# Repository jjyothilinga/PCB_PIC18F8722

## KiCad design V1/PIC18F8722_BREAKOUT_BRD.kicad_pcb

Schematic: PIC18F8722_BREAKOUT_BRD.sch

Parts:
C1: 10uF/16V
C2, C3, C4, C5, C6, C7: 0.1uF
C8: 1uF/16V
D1: LED
D2: PWR_LED
IC1: PIC18F8722; microchip-2-TQFP80
P1: PGM_CONN
P2: CONN _1_20
P3: CONN_21_40
P4: CONN_41_60
P5: CONN_61_80
P7, P9: PWR_CON
R1, R4: 10K
R2: 1K2
R3: 1K
SW1: SW_PUSH

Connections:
/AVDD: C1.1, C2.1, C3.1, C4.1, C5.1, C6.1, C7.1, IC1.12 (VDD), IC1.25 (AVDD), IC1.32 (VDD@1), IC1.48 (VDD@2), IC1.71 (VDD@3), P1.2, P2.12, P3.5, P3.12, P4.8, P5.11, P7.2 (PM), P9.2 (PM), R1.1, R2.1, R3.1, R4.1
/HB_LED: D1.2 (K), IC1.5 (RG0/ECCP3/P3A), P2.5
/MCLR: C8.1, IC1.9 (RG5/-MCLR/VPP), P1.1, P2.9, R4.2, SW1.2
/PGC: IC1.52 (RB6/KBI2/PGC), P1.5, P4.12
/PGD: IC1.47 (RB7/KBI3/PGD), P1.4, P4.7
/RA0: IC1.30 (RA0/AN0), P3.10
/RA1: IC1.29 (RA1/AN1), P3.9
/RA2: IC1.28 (RA2/AN2/VREF-), P3.8
/RA3: IC1.27 (RA3/AN3/VREF+), P3.7
/RA4: IC1.34 (RA4/T0CKI), P3.14, R1.2
/RA5: IC1.33 (RA5/AN4/HLVDIN), P3.13
/RA6: IC1.50 (OSC2/CLKO/RA6), P4.10
/RA7: IC1.49 (OSC1/CLKI/RA7), P4.9
/RB0: IC1.58 (RB0/INT0), P4.18
/RB1: IC1.57 (RB1/INT1), P4.17
/RB2: IC1.56 (RB2/INT2), P4.16
/RB3: IC1.55 (RB3/INT3/ECCP2/P2A), P4.15
/RB4: IC1.54 (RB4/KBI0), P4.14
/RB5: IC1.53 (RB5/KBI1/PGM), P4.13
/RC0: IC1.36 (RC0/T1OSO/T13CKI), P3.16
/RC1: IC1.35 (RC1/T1OSI/ECCP2/P2A), P3.15
/RC2: IC1.43 (RC2/ECCP1/P1A), P4.3
/RC3: IC1.44 (RC3/SCK1/SCL1), P4.4
/RC4: IC1.45 (RC4/SDI1/SDA1), P4.5
/RC5: IC1.46 (RC5/SDO1), P4.6
/RC6: IC1.37 (RC6/TX1/CK1), P3.17
/RC7: IC1.38 (RC7/RX1/DT1), P3.18
/RD0: IC1.72 (RD0/AD0/PSP0), P5.12
/RD1: IC1.69 (RD1/AD1/PSP1), P5.9
/RD2: IC1.68 (RD2/AD2/PSP2), P5.8
/RD3: IC1.67 (RD3/AD3/PSP3), P5.7
/RD4: IC1.66 (RD4/AD4/PSP4/SDO2), P5.6
/RD5: IC1.65 (RD5/AD5/PSP5/SDI2/SDA2), P5.5
/RD6: IC1.64 (RD6/AD6/PSP6/SCK2/SCL2), P5.4
/RD7: IC1.63 (RD7/AD7/PSP7/-SS2), P5.3
/RE0: IC1.4 (RE0/AD8/-RD/P2D), P2.4
/RE1: IC1.3 (RE1/AD9/-WR/P2C), P2.3
/RE2: IC1.78 (RE2/AD10/-CS/P2B), P5.18
/RE3: IC1.77 (RE3/AD11/P3C), P5.17
/RE4: IC1.76 (RE4/AD12/P3B), P5.16
/RE5: IC1.75 (RE5/AD13/P1C), P5.15
/RE6: IC1.74 (RE6/AD14/P1B), P5.14
/RE7: IC1.73 (RE7/AD15/ECCP2/P2A), P5.13
/RF0: IC1.24 (RF0/AN5), P3.4
/RF1: IC1.23 (RF1/AN6/C2OUT), P3.3
/RF2: IC1.18 (RF2/AN7/C1OUT), P2.18
/RF3: IC1.17 (RF3/AN8), P2.17
/RF4: IC1.16 (RF4/AN9), P2.16
/RF5: IC1.15 (RF5/AN10/CVREF), P2.15
/RF6: IC1.14 (RF6/AN11), P2.14
/RF7: IC1.13 (RF7/-SS1), P2.13
/RG1: IC1.6 (RG1/TX2/CK2), P2.6
/RG2: IC1.7 (RG2/RX2/DT2), P2.7
/RG3: IC1.8 (RG3/CCP4/P3D), P2.8
/RG4: IC1.10 (RG4/CCP4/C3D), P2.10
/RH0: IC1.79 (RH0/A16), P5.19
/RH1: IC1.80 (RH1/A17), P5.20
/RH2: IC1.1 (RH2/A18), P2.1
/RH3: IC1.2 (RH3/A19), P2.2
/RH4: IC1.22 (RH4/AN12/P3C), P3.2
/RH5: IC1.21 (RH5/AN13/P3B), P3.1
/RH6: IC1.20 (RH6/AN14/P1C), P2.20
/RH7: IC1.19 (RH7/AN15/P1B), P2.19
/RJ0: IC1.62 (RJ0/ALE), P5.2
/RJ1: IC1.61 (RJ1/-OE), P5.1
/RJ2: IC1.60 (RJ2/-WRL), P4.20
/RJ3: IC1.59 (RJ3/-WRH), P4.19
/RJ4: IC1.39 (RJ4/BA0), P3.19
/RJ5: IC1.40 (RJ5/-CE), P3.20
/RJ6: IC1.41 (RJ6/-LB), P4.1
/RJ7: IC1.42 (RJ7/-UB), P4.2
GND: C1.2, C2.2, C3.2, C4.2, C5.2, C6.2, C7.2, C8.2, D2.2 (K), IC1.11 (VSS), IC1.26 (AVSS), IC1.31 (VSS@1), IC1.51 (VSS@2), IC1.70 (VSS@3), P1.3, P2.11, P3.6, P3.11, P4.11, P5.10, P7.1, P9.1, SW1.1
unnamed: D2.1 (A), R3.2
unnamed: D1.1 (A), R2.2

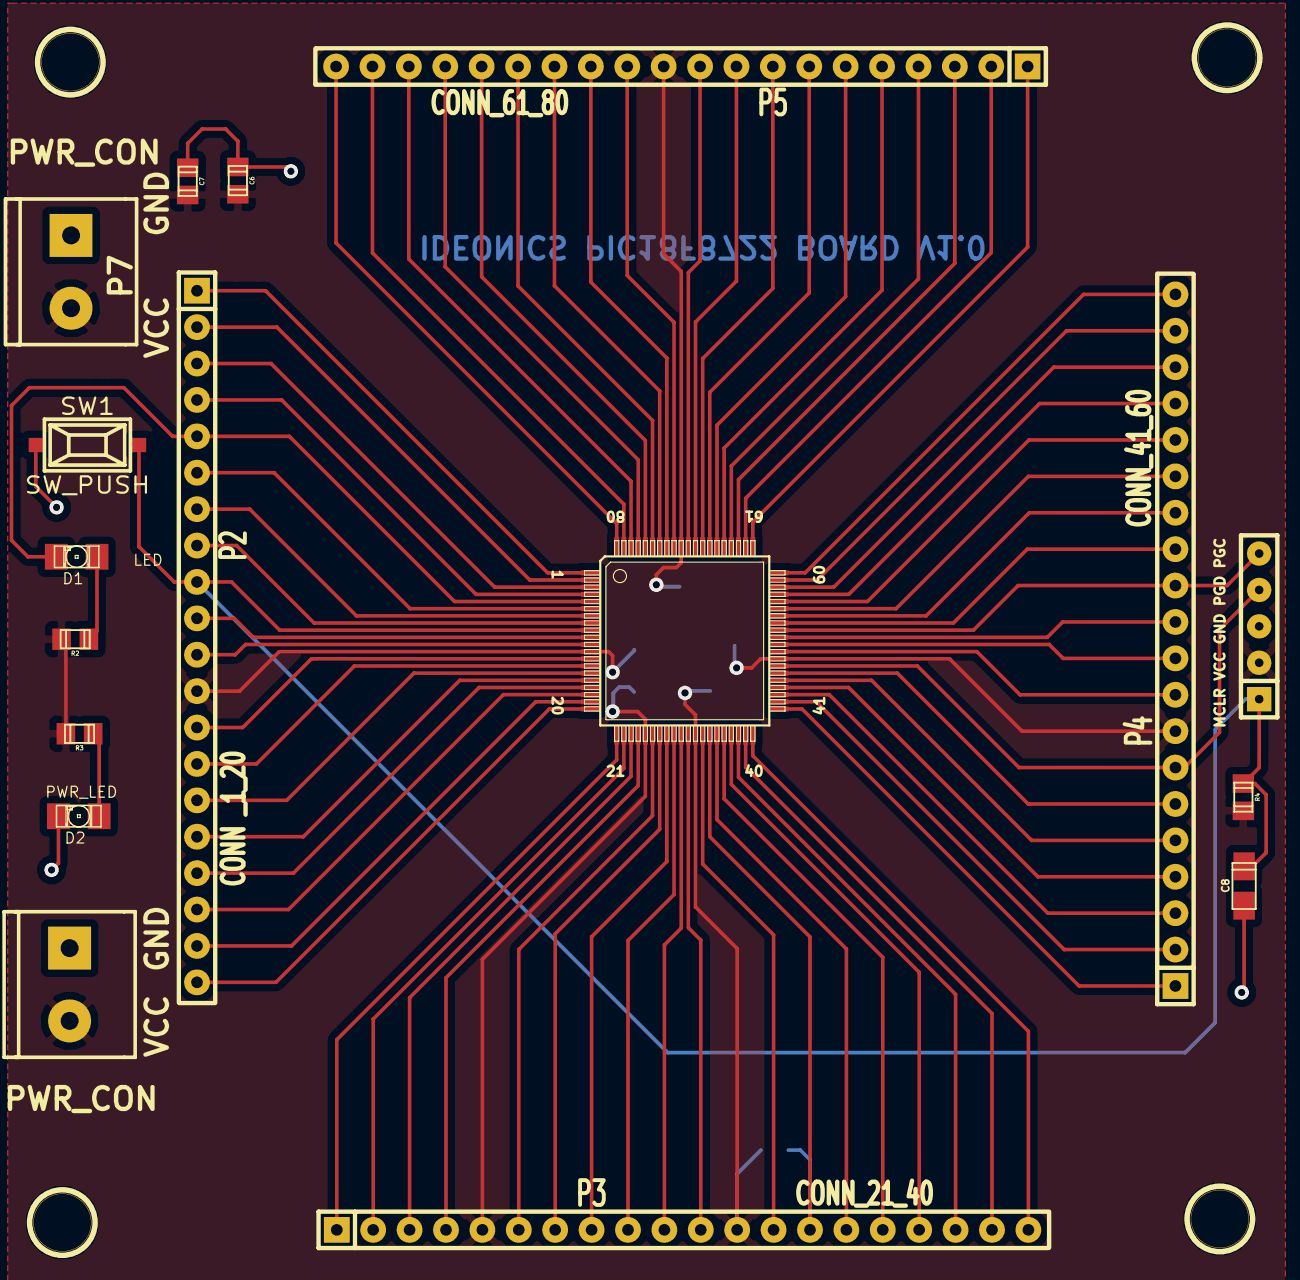
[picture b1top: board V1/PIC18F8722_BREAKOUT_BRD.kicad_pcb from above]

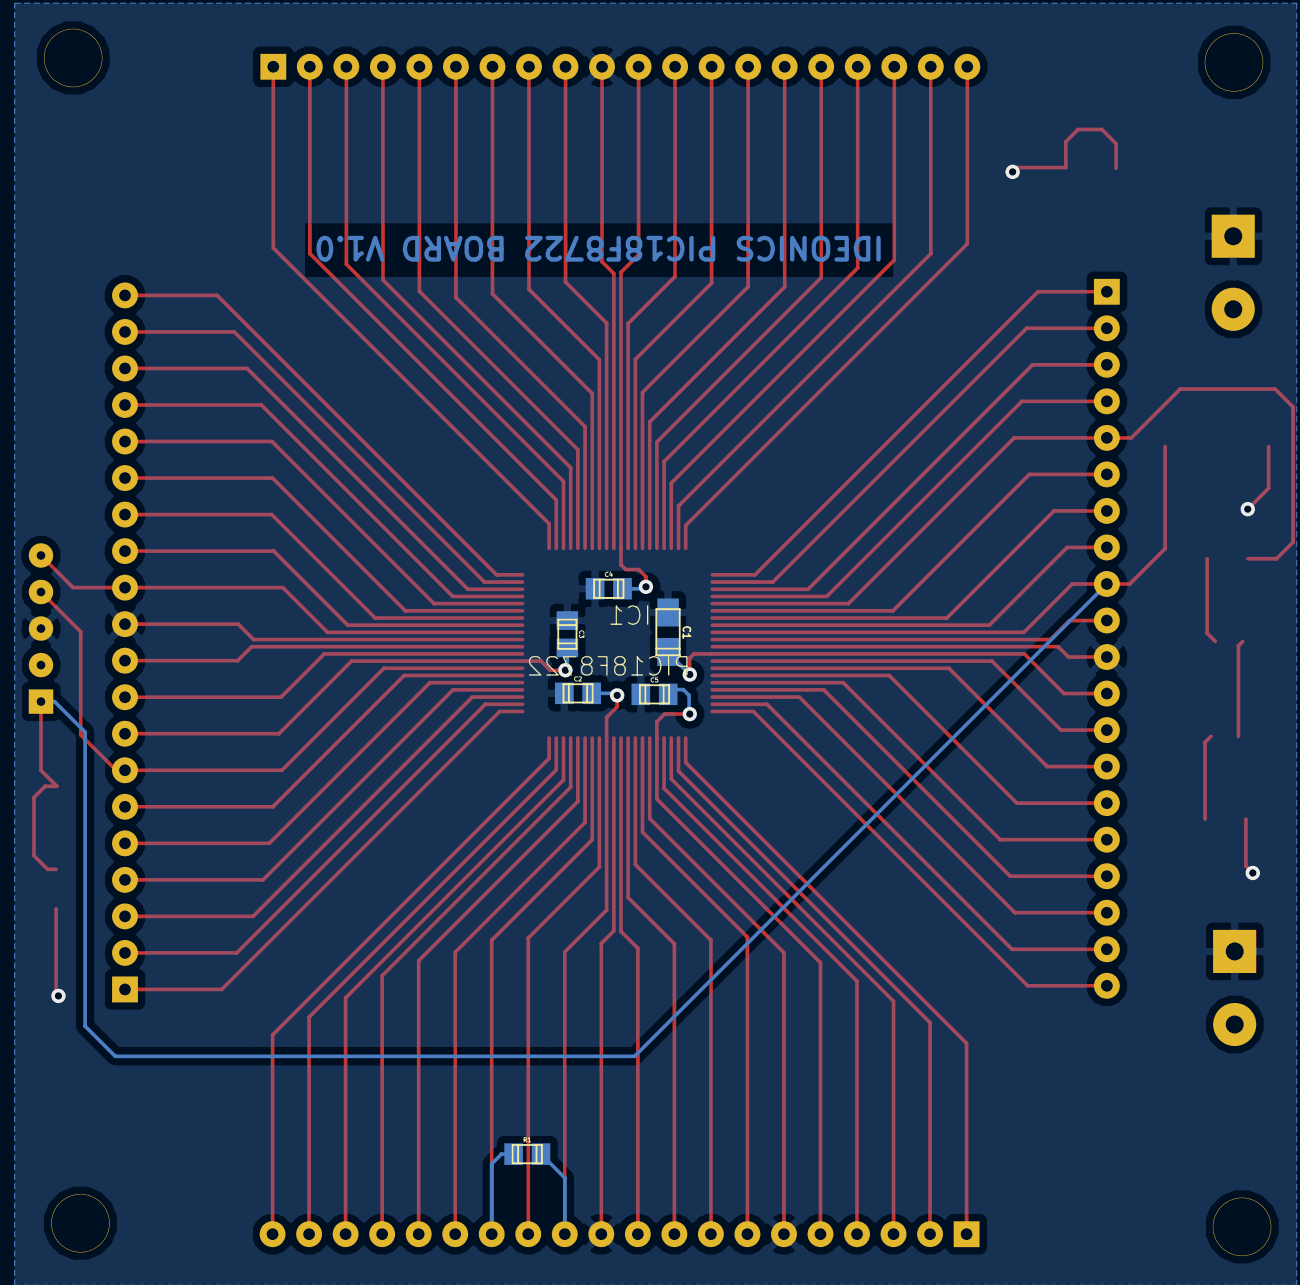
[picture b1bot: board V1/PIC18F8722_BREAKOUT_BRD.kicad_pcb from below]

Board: 2 copper layers, 27 parts (6 on the bottom side), 74 nets.

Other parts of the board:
1PIN, 1PIN#2, 1PIN#3, 1PIN#4: P***; 1pin

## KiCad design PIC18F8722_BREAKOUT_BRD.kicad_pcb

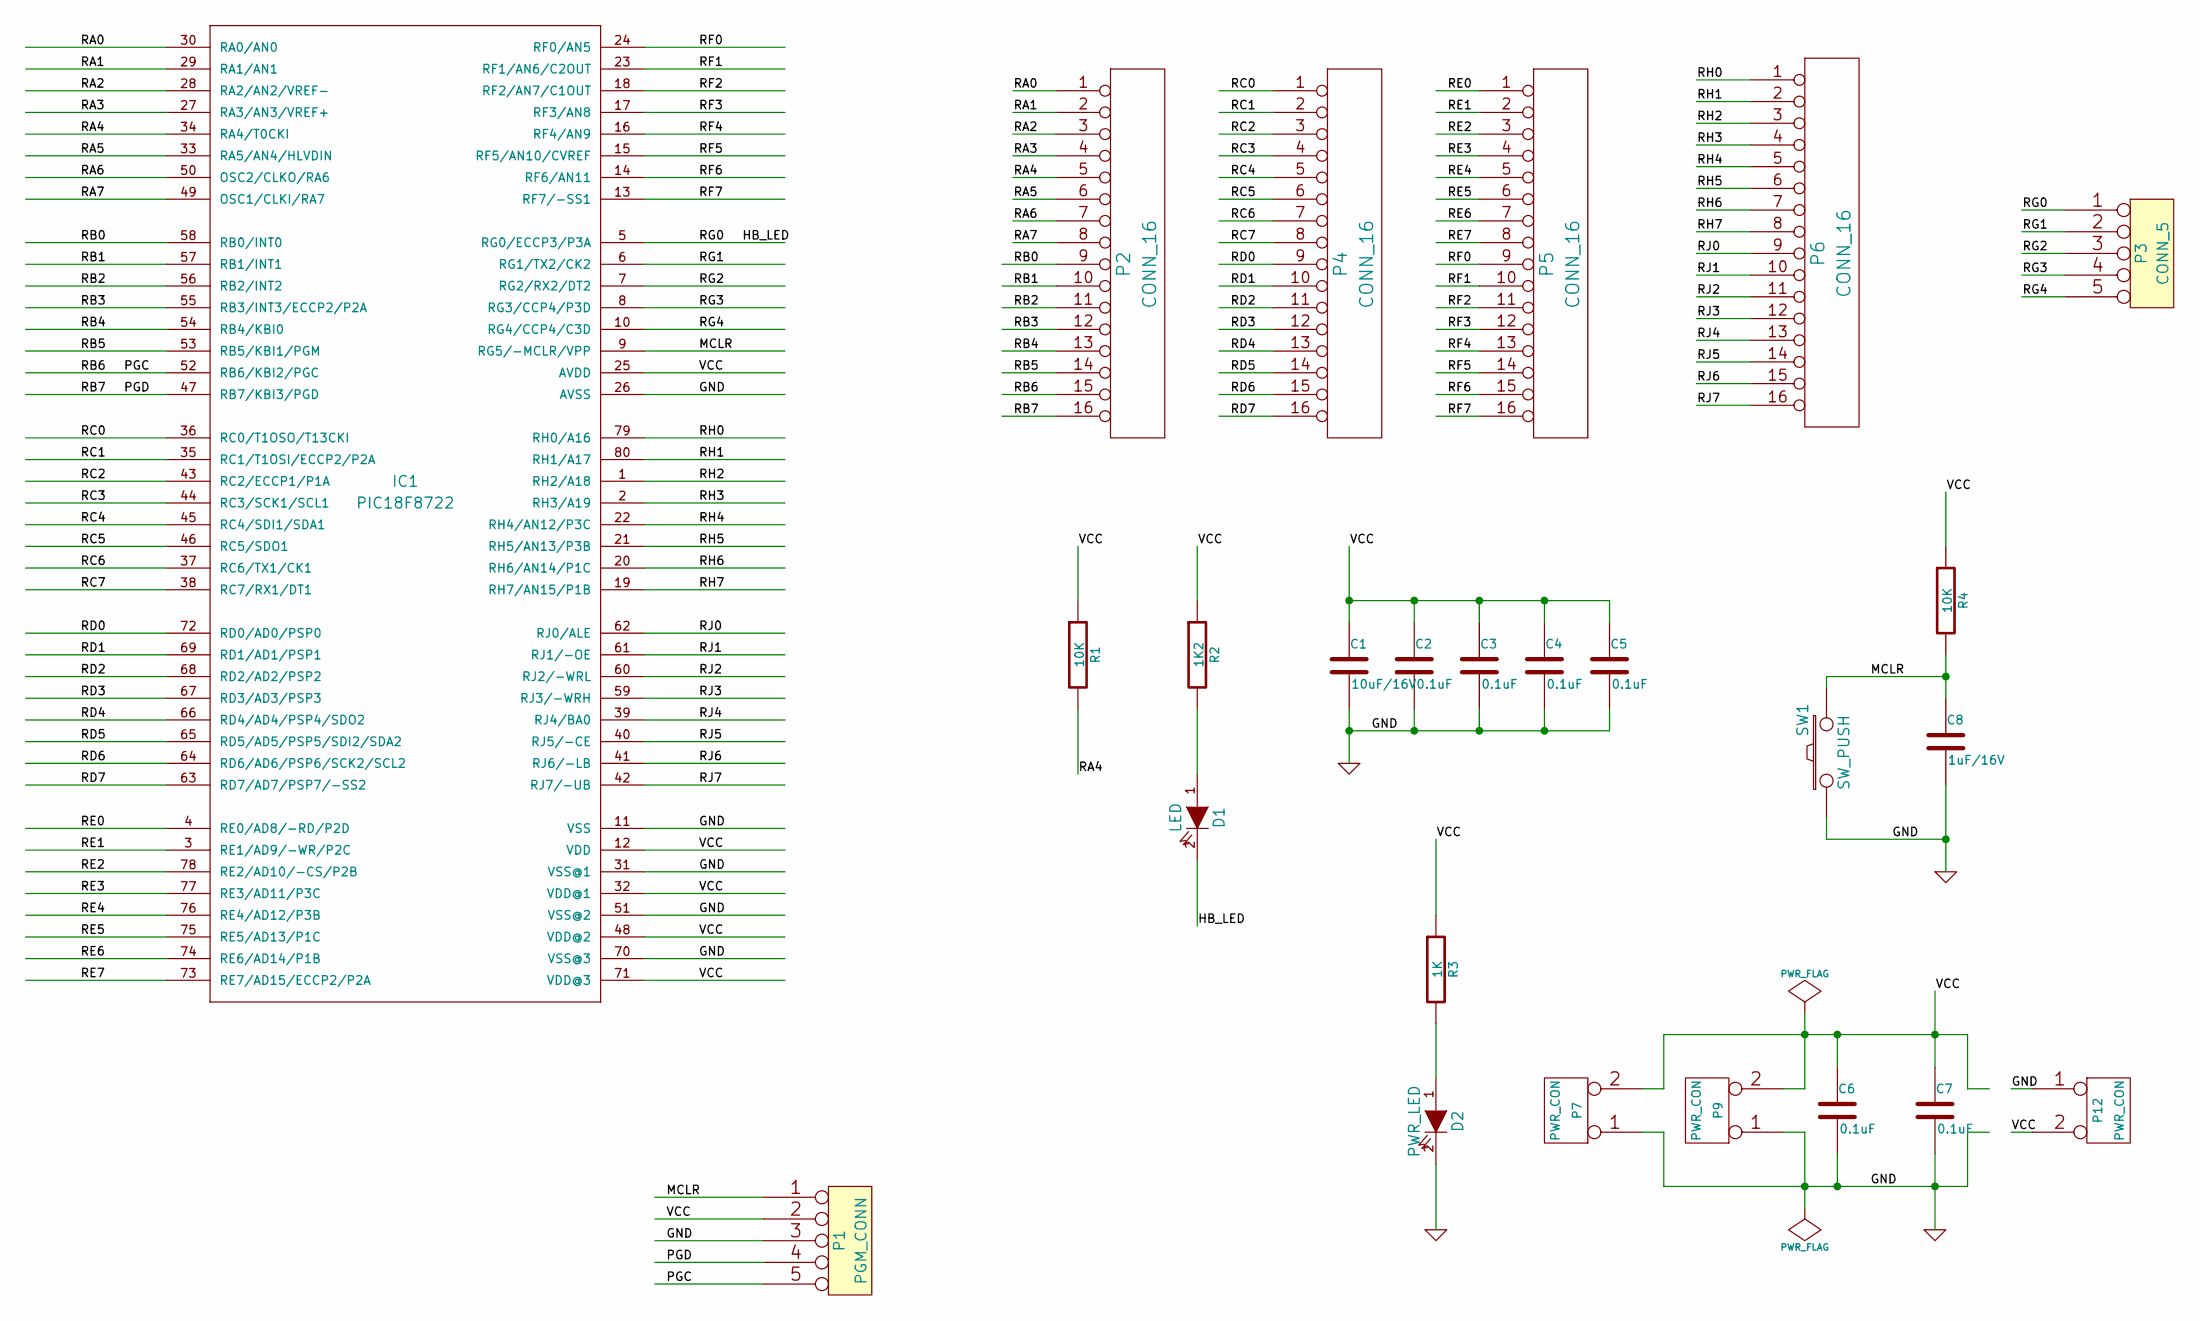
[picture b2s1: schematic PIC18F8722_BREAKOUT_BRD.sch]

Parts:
C1: 10uF/16V
C2, C3, C4, C5, C6, C7: 0.1uF
C8: 1uF/16V
D1: LED
D2: PWR_LED
IC1: PIC18F8722; microchip-2-TQFP80
P1: PGM_CONN
P2, P4, P5, P6: CONN_16
P3: CONN_5
P7, P9, P12: PWR_CON
R1, R4: 10K
R2: 1K2
R3: 1K
SW1: SW_PUSH

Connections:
/HB_LED: D1.2 (K), IC1.5 (RG0/ECCP3/P3A), P3.1
/MCLR: C8.1, IC1.9 (RG5/-MCLR/VPP), P1.1, R4.2, SW1.2
/PGC: IC1.52 (RB6/KBI2/PGC), P1.5, P2.15
/PGD: IC1.47 (RB7/KBI3/PGD), P1.4, P2.16
/RA0: IC1.30 (RA0/AN0), P2.1
/RA1: IC1.29 (RA1/AN1), P2.2
/RA2: IC1.28 (RA2/AN2/VREF-), P2.3
/RA3: IC1.27 (RA3/AN3/VREF+), P2.4
/RA4: IC1.34 (RA4/T0CKI), P2.5, R1.2
/RA5: IC1.33 (RA5/AN4/HLVDIN), P2.6
/RA6: IC1.50 (OSC2/CLKO/RA6), P2.7
/RA7: IC1.49 (OSC1/CLKI/RA7), P2.8
/RB0: IC1.58 (RB0/INT0), P2.9
/RB1: IC1.57 (RB1/INT1), P2.10
/RB2: IC1.56 (RB2/INT2), P2.11
/RB3: IC1.55 (RB3/INT3/ECCP2/P2A), P2.12
/RB4: IC1.54 (RB4/KBI0), P2.13
/RB5: IC1.53 (RB5/KBI1/PGM), P2.14
/RC0: IC1.36 (RC0/T1OSO/T13CKI), P4.1
/RC1: IC1.35 (RC1/T1OSI/ECCP2/P2A), P4.2
/RC2: IC1.43 (RC2/ECCP1/P1A), P4.3
/RC3: IC1.44 (RC3/SCK1/SCL1), P4.4
/RC4: IC1.45 (RC4/SDI1/SDA1), P4.5
/RC5: IC1.46 (RC5/SDO1), P4.6
/RC6: IC1.37 (RC6/TX1/CK1), P4.7
/RC7: IC1.38 (RC7/RX1/DT1), P4.8
/RD0: IC1.72 (RD0/AD0/PSP0), P4.9
/RD1: IC1.69 (RD1/AD1/PSP1), P4.10
/RD2: IC1.68 (RD2/AD2/PSP2), P4.11
/RD3: IC1.67 (RD3/AD3/PSP3), P4.12
/RD4: IC1.66 (RD4/AD4/PSP4/SDO2), P4.13
/RD5: IC1.65 (RD5/AD5/PSP5/SDI2/SDA2), P4.14
/RD6: IC1.64 (RD6/AD6/PSP6/SCK2/SCL2), P4.15
/RD7: IC1.63 (RD7/AD7/PSP7/-SS2), P4.16
/RE0: IC1.4 (RE0/AD8/-RD/P2D), P5.1
/RE1: IC1.3 (RE1/AD9/-WR/P2C), P5.2
/RE2: IC1.78 (RE2/AD10/-CS/P2B), P5.3
/RE3: IC1.77 (RE3/AD11/P3C), P5.4
/RE4: IC1.76 (RE4/AD12/P3B), P5.5
/RE5: IC1.75 (RE5/AD13/P1C), P5.6
/RE6: IC1.74 (RE6/AD14/P1B), P5.7
/RE7: IC1.73 (RE7/AD15/ECCP2/P2A), P5.8
/RF0: IC1.24 (RF0/AN5), P5.9
/RF1: IC1.23 (RF1/AN6/C2OUT), P5.10
/RF2: IC1.18 (RF2/AN7/C1OUT), P5.11
/RF3: IC1.17 (RF3/AN8), P5.12
/RF4: IC1.16 (RF4/AN9), P5.13
/RF5: IC1.15 (RF5/AN10/CVREF), P5.14
/RF6: IC1.14 (RF6/AN11), P5.15
/RF7: IC1.13 (RF7/-SS1), P5.16
/RG1: IC1.6 (RG1/TX2/CK2), P3.2
/RG2: IC1.7 (RG2/RX2/DT2), P3.3
/RG3: IC1.8 (RG3/CCP4/P3D), P3.4
/RG4: IC1.10 (RG4/CCP4/C3D), P3.5
/RH0: IC1.79 (RH0/A16), P6.1
/RH1: IC1.80 (RH1/A17), P6.2
/RH2: IC1.1 (RH2/A18), P6.3
/RH3: IC1.2 (RH3/A19), P6.4
/RH4: IC1.22 (RH4/AN12/P3C), P6.5
/RH5: IC1.21 (RH5/AN13/P3B), P6.6
/RH6: IC1.20 (RH6/AN14/P1C), P6.7
/RH7: IC1.19 (RH7/AN15/P1B), P6.8
/RJ0: IC1.62 (RJ0/ALE), P6.9
/RJ1: IC1.61 (RJ1/-OE), P6.10
/RJ2: IC1.60 (RJ2/-WRL), P6.11
/RJ3: IC1.59 (RJ3/-WRH), P6.12
/RJ4: IC1.39 (RJ4/BA0), P6.13
/RJ5: IC1.40 (RJ5/-CE), P6.14
/RJ6: IC1.41 (RJ6/-LB), P6.15
/RJ7: IC1.42 (RJ7/-UB), P6.16
/VCC: C1.1, C2.1, C3.1, C4.1, C5.1, C6.1, C7.1, IC1.12 (VDD), IC1.25 (AVDD), IC1.32 (VDD@1), IC1.48 (VDD@2), IC1.71 (VDD@3), P1.2, P7.2 (PM), P9.2 (PM), P12.2 (PM), R1.1, R2.1, R3.1, R4.1
GND: C1.2, C2.2, C3.2, C4.2, C5.2, C6.2, C7.2, C8.2, D2.2 (K), IC1.11 (VSS), IC1.26 (AVSS), IC1.31 (VSS@1), IC1.51 (VSS@2), IC1.70 (VSS@3), P1.3, P7.1, P9.1, P12.1, SW1.1
unnamed: D1.1 (A), R2.2
unnamed: D2.1 (A), R3.2

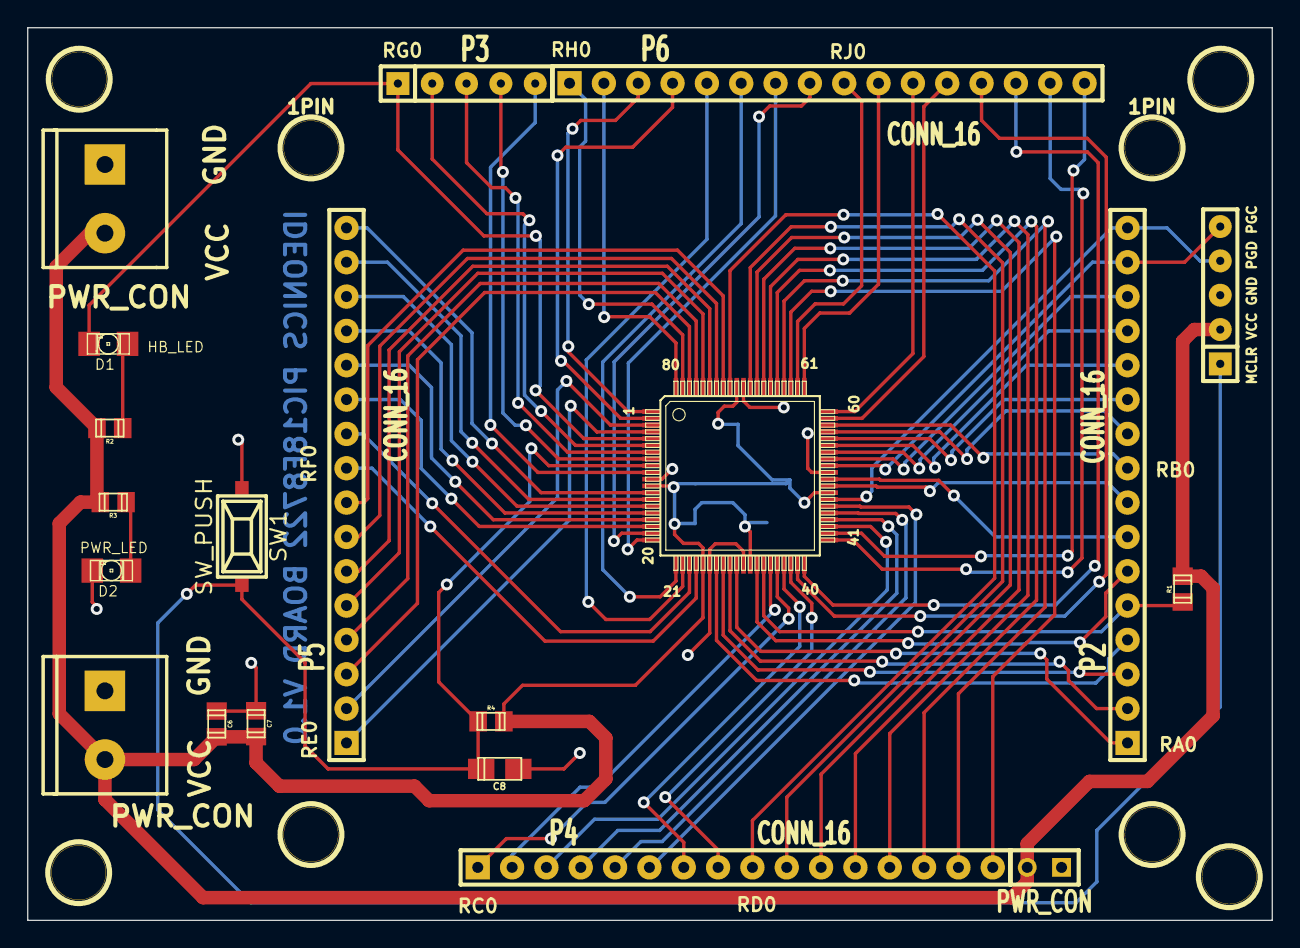
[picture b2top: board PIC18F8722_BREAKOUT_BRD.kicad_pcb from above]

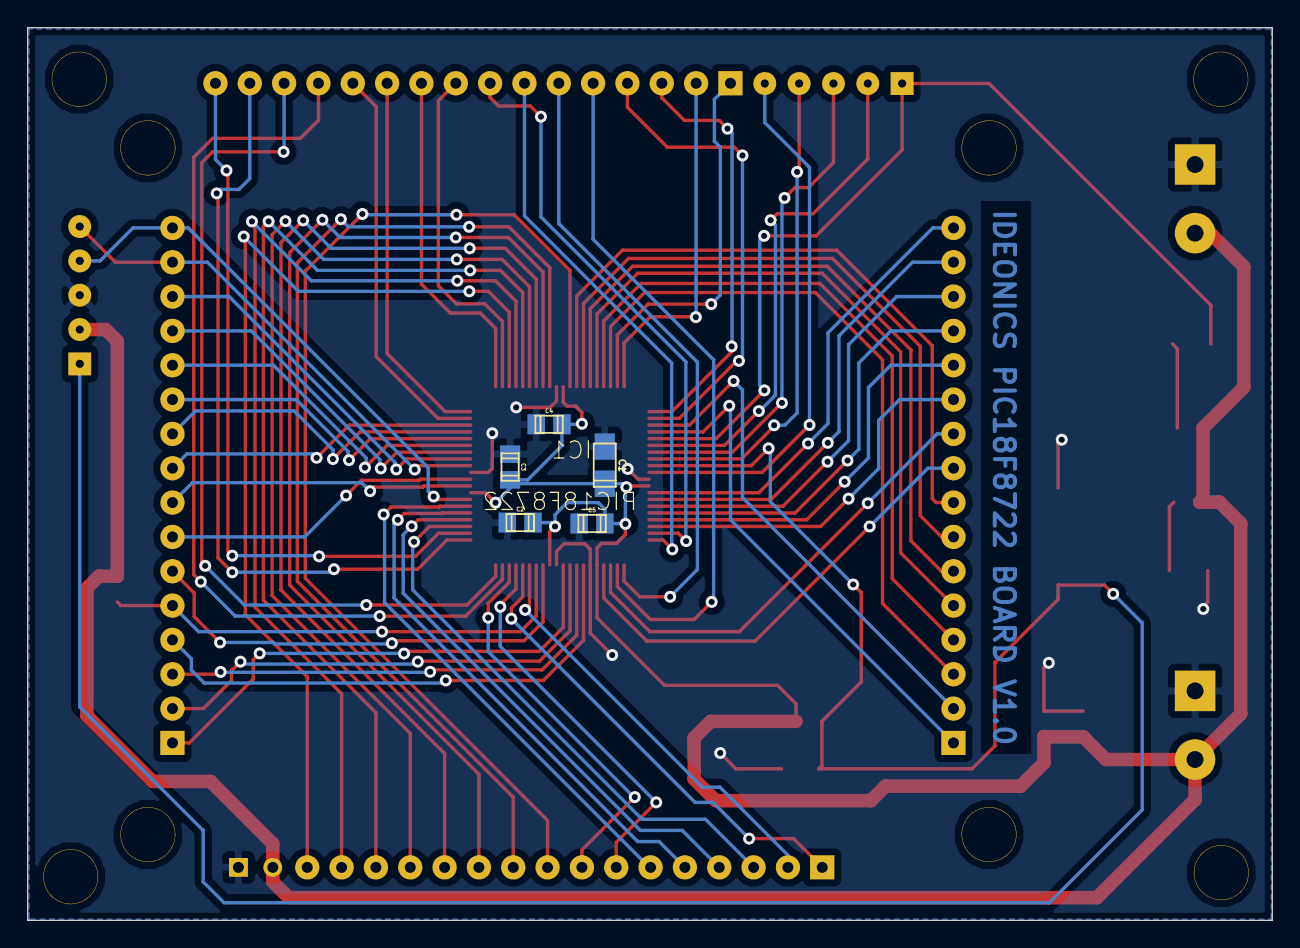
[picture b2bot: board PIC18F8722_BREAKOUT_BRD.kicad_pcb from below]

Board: 2 copper layers, 92.1 x 66.0 mm, 33 parts (5 on the bottom side), 74 nets.

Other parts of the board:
1PIN, 1PIN#2, 1PIN#3, 1PIN#4, 1PIN#5, 1PIN#6, 1PIN#7, 1PIN#8: P***; 1pin

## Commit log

2015-03-06 :circus_tent: Added .gitattributes & .gitignore files
2015-03-06 Completed
2015-03-13 Updated as per requirement
2015-03-13 Via dimension updated
2015-07-24 V2 18f87k22 added
